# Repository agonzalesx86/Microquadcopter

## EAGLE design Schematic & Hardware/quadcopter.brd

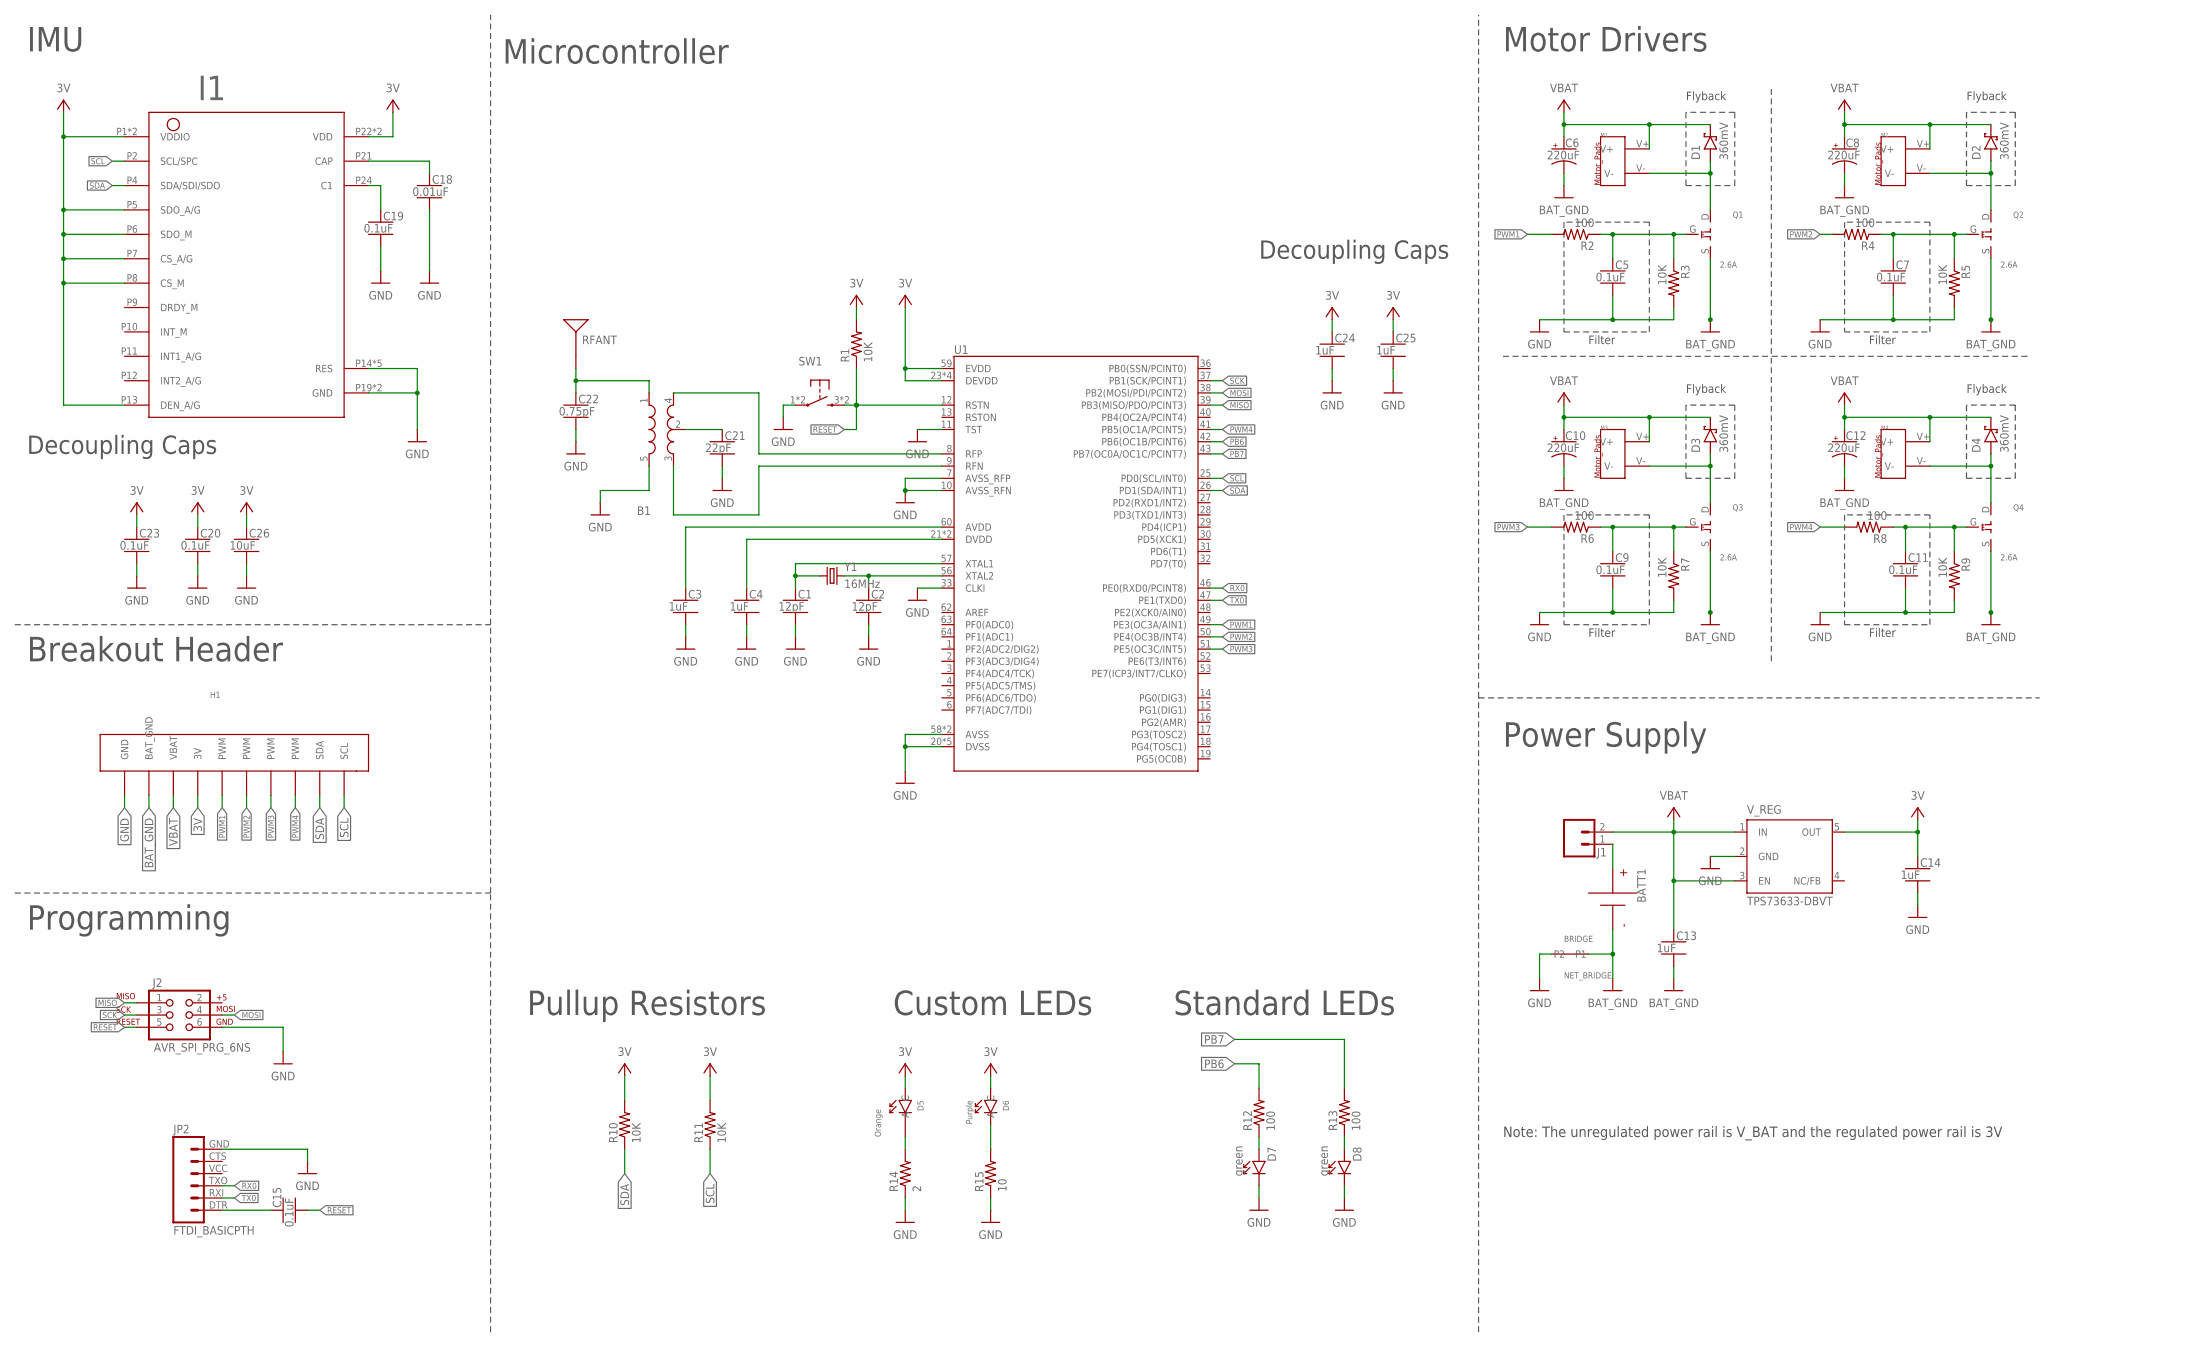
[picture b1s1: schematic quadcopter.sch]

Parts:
B1: BALUN0805; BALUN
BATT1: BATTERY-HUBSAN-W/HOLDER; BATTERY-W/HOLDER-380MAH-HUBSAN
BRIDGE: NET_BRIDGE
C1, C2: 12pF; CAPC2012X140_HS
C3, C4, C13, C14, C24, C25: 1uF; CAPC2012X140_HS
C5, C7, C9, C11, C15, C19, C20, C23: 0.1uF; CAPC2012X140_HS
C6, C8, C10, C12: 220uF; CAPMP7343X310_HS
C18: 0.01uF; CAPC2012X140_HS
C21: 22pF; CAPC2012X140_HS
C22: 0.75pF; CAPC2012X140_HS
C26: 10uF; CAPC2012X140_HS
D1, D2, D3, D4: 360mV; SOD3716X135_HS
D5: Orange; LED_ORANGE
D6: Purple; LED_PURPLE
D7, D8: green; LEDSC125X200X120-2_HS
H1: BREAKOUT_HEADER
I1: IMU_LSM9DS1TR
J1: MALE_HEADER_2POS-2X1-0.1IN; MALE_HEADER_2X1_0.1IN
J2: AVR_SPI_PRG_6NS; 2X3-NS
JP2: FTDI_BASICPTH; FTDI_BASIC
M1, M2, M3, M4: MOTOR_PADS
Q1, Q2, Q3, Q4: 2.6A; MOSFET_N-CHANNEL
R1, R3, R5, R7, R9, R10, R11: 10K; RESC2012X60_HS
R2, R4, R6, R8, R12, R13: 100; RESC2012X60_HS
R14: 2; RESISTOR_0805
R15: 10; RESISTOR_0805
RFANT: ANTENNA2SMD5; ANTENNA-CHIP5
SW1: PUSHBUTTON_SMD-VERTICAL-1; TE_FSM8JSMA_HS
U1: ATMEGA128RFA1; QFN-64
V_REG: TPS73633-DBVT; SOT23-DBV
Y1: 16MHz; CRYSTAL-SMD-5X3

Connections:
3V: C14.1, C20.1, C23.1, C24.1, C25.1, C26.1, D5.A, D6.A, H1.1 (3V), I1.P1 (VDDIO), I1.P3 (VDDIO), I1.P5 (SDO_A/G), I1.P6 (SDO_M), I1.P7 (CS_A/G), I1.P8 (CS_M), I1.P13 (DEN_A/G), I1.P22 (VDD), I1.P23 (VDD), R1.2, R10.2, R11.2, U1.23 (DEVDD), U1.34 (DEVDD), U1.44 (DEVDD), U1.54 (DEVDD), U1.59 (EVDD), V_REG.5 (OUT)
BAT_GND: BATT1.- (N), BRIDGE.P2, C6.2 (-), C8.2 (-), C10.2 (-), C12.2 (-), C13.2, H1.2 (BAT_GND), Q1.S, Q2.S, Q3.S, Q4.S
GND: B1.5 (GND), BRIDGE.P1, C1.2, C2.2, C3.2, C4.2, C5.2, C7.2, C9.2, C11.2, C14.2, C18.2, C19.2, C20.2, C21.2, C22.2, C23.2, C24.2, C25.2, C26.2, D7.C, D8.C, H1.3 (GND), I1.P14 (RES), I1.P15 (RES), I1.P16 (RES), I1.P17 (RES), I1.P18 (RES), I1.P19 (GND), I1.P20 (GND), J2.6, JP2.GND (6), R3.2, R5.2, R7.2, R9.2, R14.IN (1), R15.IN (1), SW1.1, SW1.2 (1), U1.7 (AVSS_RFP), U1.10 (AVSS_RFN), U1.11 (TST), U1.20 (DVSS), U1.24 (DVSS), U1.33 (CLKI), U1.35 (DVSS), U1.45 (DVSS), U1.55 (DVSS), U1.58 (AVSS), U1.61 (AVSS), V_REG.2 (GND)
MISO: J2.1, U1.39 (PB3(MISO/PDO/PCINT3))
MOSI: J2.4, U1.38 (PB2(MOSI/PDI/PCINT2))
unnamed: D6.C, R15.OUT (2)
unnamed: B1.4 (OUT1), U1.8 (RFP)
unnamed: B1.3 (OUT2), U1.9 (RFN)
unnamed: C4.1, U1.21 (DVDD), U1.22 (DVDD)
unnamed: C2.1, U1.56 (XTAL2), Y1.3 (2)
unnamed: C3.1, U1.60 (AVDD)
unnamed: C1.1, U1.57 (XTAL1), Y1.1
unnamed: D1.A, M1.V-, Q1.D
unnamed: D5.C, R14.OUT (2)
unnamed: C7.1, Q2.G, R4.1, R5.1
unnamed: D2.A, M2.V-, Q2.D
unnamed: C9.1, Q3.G, R6.1, R7.1
unnamed: C5.1, Q1.G, R2.1, R3.1
unnamed: D3.A, M3.V-, Q3.D
unnamed: C11.1, Q4.G, R8.1, R9.1
unnamed: D7.A, R12.1
unnamed: BATT1.+, J1.1
unnamed: B1.2 (GND), C21.1
unnamed: D4.A, M4.V-, Q4.D
unnamed: C18.1, I1.P21 (CAP)
unnamed: C19.1, I1.P24 (C1)
unnamed: B1.1 (IN), C22.1, RFANT.FEED
unnamed: C15.1, JP2.DTR (1)
unnamed: D8.A, R13.1
PB6: R12.2, U1.42 (PB6(OC1B/PCINT6))
PB7: R13.2, U1.43 (PB7(OC0A/OC1C/PCINT7))
PWM1: H1.4 (PWM), R2.2, U1.49 (PE3(OC3A/AIN1))
PWM2: H1.5 (PWM), R4.2, U1.50 (PE4(OC3B/INT4))
PWM3: H1.6 (PWM), R6.2, U1.51 (PE5(OC3C/INT5))
PWM4: H1.7 (PWM), R8.2, U1.41 (PB5(OC1A/PCINT5))
RESET: C15.2, J2.5, R1.1, SW1.3 (2), SW1.4 (2), U1.12 (RSTN)
RX0: JP2.TXO (3), U1.46 (PE0(RXD0/PCINT8))
SCK: J2.3, U1.37 (PB1(SCK/PCINT1))
SCL: H1.8 (SCL), I1.P2 (SCL/SPC), R11.1, U1.25 (PD0(SCL/INT0))
SDA: H1.9 (SDA), I1.P4 (SDA/SDI/SDO), R10.1, U1.26 (PD1(SDA/INT1))
TX0: JP2.RXI (2), U1.47 (PE1(TXD0))
VBAT: C6.1 (+), C8.1 (+), C10.1 (+), C12.1 (+), C13.1, D1.C, D2.C, D3.C, D4.C, H1.10 (VBAT), J1.2, M1.V+, M2.V+, M3.V+, M4.V+, V_REG.1 (IN), V_REG.3 (EN)

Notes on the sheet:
Microcontroller
Motor Drivers
Power Supply
Breakout Header
IMU
Programming
Filter
Flyback
Note: The unregulated power rail is V_BAT and the regulated power rail is 3V
Pullup Resistors
Custom LEDs
Standard LEDs
Decoupling Caps

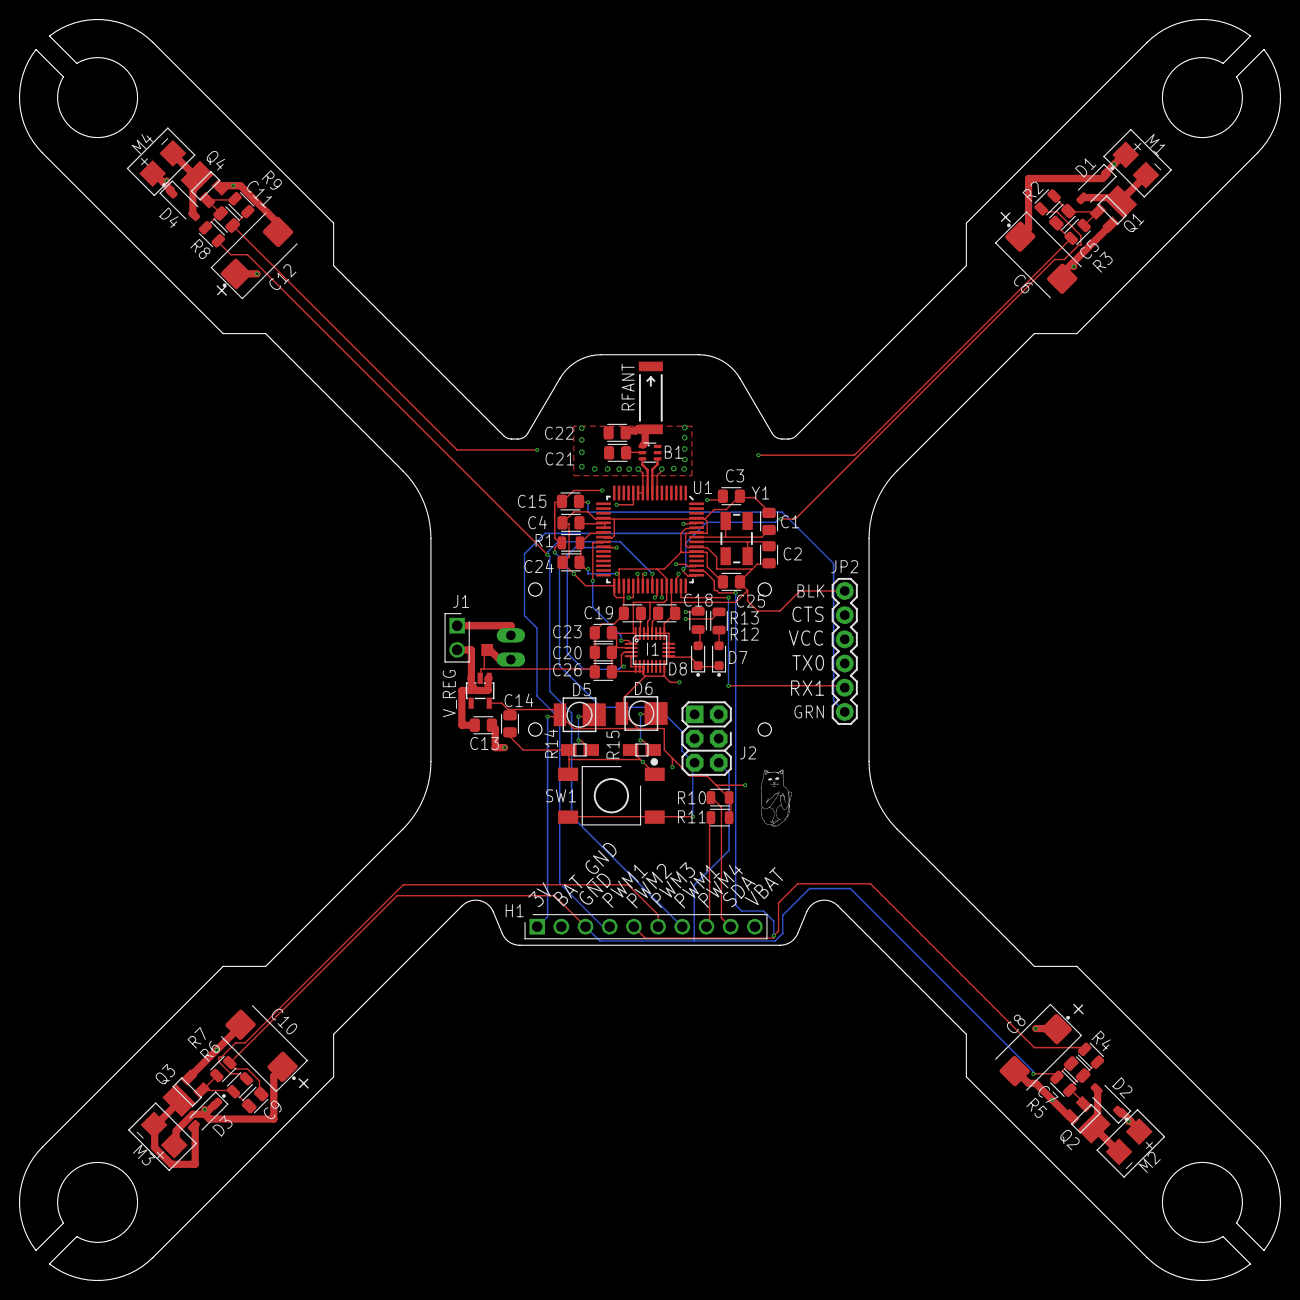
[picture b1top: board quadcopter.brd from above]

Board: 4 copper layers, 132.4 x 132.4 mm, 69 parts (1 on the bottom side), 42 nets.

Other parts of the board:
U$3: UCSD_LOGO
